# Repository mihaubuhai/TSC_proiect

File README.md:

# OpenBook e-book reader

## BOM - Bill of Materials

| Component                        | Datasheet | Vendor |
| ----------------------------------- | -------| --------|
| 112A-TAAR-R03_ATTEND                | [datasheet](https://www.attend.com.tw/en/product.php?act=view&id=253) | [vendor](https://www.digikey.com/en/products/detail/attend-technology/112A-TAAR-R03/17633923) |
| BD5229G-TR                          | [datasheet](https://www.digikey.ph/en/products/detail/rohm-semiconductor/BD5229G-TR/658502) | [vendor](https://www.digikey.ph/en/products/detail/rohm-semiconductor/BD5229G-TR/658502) |
| BUTTON_COSYOMV1                     | [datasheet](https://components101.com/switches/push-button) | [vendor](https://uk.farnell.com/wurth-elektronik/430182043816/switch-160gf-6x6mm-smd-4-3mm-act/dp/2065105?CMP=GRHB-OEMSECRETS101) |
| CPH3225A                            | [datasheet](https://www.digikey.com/en/products/detail/seiko-instruments/CPH3225A/8692444) | [vendor](https://www.digikey.com/en/products/detail/seiko-instruments/CPH3225A/8692444) |
| DS3231SN                            | [datasheet](https://www.digikey.com/en/products/detail/analog-devices-inc-maxim-integrated/DS3231SN/1197576) | [vendor](https://www.digikey.com/en/products/detail/analog-devices-inc-maxim-integrated/DS3231SN/1197576) |
| BME680                              | [datasheet](https://www.sparkfun.com/sparkfun-environmental-sensor-breakout-bme680-qwiic.html) | [vendor](https://www.sparkfun.com/sparkfun-environmental-sensor-breakout-bme680-qwiic.html) |
| MCP73831                            | [datasheet](https://www.microchip.com/en-us/product/mcp73831) | [vendor](https://www.microchipdirect.com/product/MCP73831T-2ADI/OT) |
| C6-WROOM-1-N8                       | [datasheet](https://www.espressif.com/sites/default/files/documentation/esp32-c6-wroom-1_wroom-1u_datasheet_en.pdf) | [vendor](https://www.adafruit.com/product/5671) |
| FH34SRJ-24S-0.5SH_99_               | [datasheet](https://www.hirose.com/product/p/CL0580-1255-6-99) | [vendor](https://www.hirose.com/product/p/CL0580-1255-6-99) |
| MAX17048G+T10                       | [datasheet](https://eu.mouser.com/ProductDetail/Analog-Devices-Maxim-Integrated/MAX17048G+T10?qs=D7PJwyCwLAoGnnn8jEPRBQ%3D%3D) | [vendor](https://eu.mouser.com/ProductDetail/Analog-Devices-Maxim-Integrated/MAX17048G+T10?qs=D7PJwyCwLAoGnnn8jEPRBQ%3D%3D) |
| MBR0530                             | [datasheet](https://www.digikey.com/en/products/detail/onsemi/MBR0530/1048783) | [vendor](https://www.digikey.com/en/products/detail/onsemi/MBR0530/1048783) |
| PGB1010603MR                        | [datasheet](https://www.digikey.com/en/products/detail/littelfuse-inc/PGB1010603MR/715755) | [vendor](https://www.digikey.com/en/products/detail/littelfuse-inc/PGB1010603MR/715755) |
| SAMACSYS_PARTS_USB4110-GF-A         | [datasheet](https://www.digikey.ro/en/products/detail/gct/USB4110-GF-A/10384547) | [vendor](https://www.digikey.ro/en/products/detail/gct/USB4110-GF-A/10384547) |
| SI1308EDL-T1-GE3                    | [datasheet](https://www.digikey.com/en/products/detail/vishay-siliconix/SI1308EDL-T1-GE3/4876435) | [vendor](https://www.digikey.com/en/products/detail/vishay-siliconix/SI1308EDL-T1-GE3/4876435) |
| SJ                                  | [datasheet](https://www.digikey.com/en/products/detail/cui-devices/SJ1-3514N/738685) | [vendor](https://www.digikey.com/en/products/detail/cui-devices/SJ1-3514N/738685) |
| USBLC6-2SC6Y                        | [datasheet](https://www.digikey.com/en/products/detail/stmicroelectronics/USBLC6-2SC6Y/2819177) | [vendor](https://www.digikey.com/en/products/detail/stmicroelectronics/USBLC6-2SC6Y/2819177) |
| W25Q512JVEIQ                        | [datasheet](https://www.digikey.com/en/products/detail/winbond-electronics/W25Q512JVEIQ/10244706) | [vendor](https://www.digikey.com/en/products/detail/winbond-electronics/W25Q512JVEIQ/10244706) |
| XC6220A331MR-G                      | [datasheet](https://www.digikey.com/en/products/detail/torex-semiconductor-ltd/XC6220B331MR-G/2138177) | [vendor](https://www.digikey.com/en/products/detail/torex-semiconductor-ltd/XC6220B331MR-G/2138177) |
| SD0805S020S1R0                      | [datasheet](https://www.digikey.com/en/products/detail/kyocera-avx/SD0805S020S1R0/3749517) | [vendor](https://www.digikey.com/en/products/detail/kyocera-avx/SD0805S020S1R0/3749517) |
| LTSPICE_C 100nF                     | [datasheet](https://www.digikey.com/en/products/detail/nextgen-components/0402B104K500HI/22601924) | [vendor](https://www.digikey.com/en/products/detail/nextgen-components/0402B104K500HI/22601924) |
| LTSPICE_C 10nF                      | [datasheet](https://www.amazon.com/ALLECIN-Electrolytic-Capacitor-0-2x0-43in-Capacitors/dp/B0CMQC587X/ref=sr_1_1_sspa?sr=8-1-spons&sp_csd=d2lkZ2V0TmFtZT1zcF9hdGY&psc=1) | [vendor](https://www.amazon.com/ALLECIN-Electrolytic-Capacitor-0-2x0-43in-Capacitors/dp/B0CMQC587X/ref=sr_1_1_sspa?sr=8-1-spons&sp_csd=d2lkZ2V0TmFtZT1zcF9hdGY&psc=1) |
| LTSPICE_C 4.7uF                     | [datasheet](https://www.amazon.com/ALLECIN-Electrolytic-Capacitor-0-2x0-43in-Capacitors/dp/B0CMQC587X/ref=sr_1_1_sspa?sr=8-1-spons&sp_csd=d2lkZ2V0TmFtZT1zcF9hdGY&psc=1) | [vendor](https://www.amazon.com/ALLECIN-Electrolytic-Capacitor-0-2x0-43in-Capacitors/dp/B0CMQC587X/ref=sr_1_1_sspa?sr=8-1-spons&sp_csd=d2lkZ2V0TmFtZT1zcF9hdGY&psc=1) |
| LTSPICE_C 1uF                       | [datasheet](https://www.amazon.com/ALLECIN-Electrolytic-Capacitor-0-2x0-43in-Capacitors/dp/B0CMQC587X/ref=sr_1_1_sspa?sr=8-1-spons&sp_csd=d2lkZ2V0TmFtZT1zcF9hdGY&psc=1) | [vendor](https://www.amazon.com/ALLECIN-Electrolytic-Capacitor-0-2x0-43in-Capacitors/dp/B0CMQC587X/ref=sr_1_1_sspa?sr=8-1-spons&sp_csd=d2lkZ2V0TmFtZT1zcF9hdGY&psc=1) |
| LTSPICE_C 0.1uF                     | [datasheet](https://www.digikey.com/en/products/detail/samsung-electro-mechanics/CL10E104KC8VPNC/20498486) | [vendor](https://www.digikey.com/en/products/detail/samsung-electro-mechanics/CL10E104KC8VPNC/20498486) |
| ADAFRUIT_LED                        | [datasheet](https://www.adafruit.com/product/4684) | [vendor](https://www.adafruit.com/product/4684) |
| ESP32_VARISTOR                      | [datasheet](https://uk.rs-online.com/web/p/varistors/9012743) | [vendor](https://uk.rs-online.com/web/p/varistors/9012743) |
| CT3528 (RCL_CPOL-EU) 100uF          | [datasheet](https://www.datasheetarchive.com/?q=ct3528) | [vendor](https://ro.mouser.com/ProductDetail/Panasonic/EEU-FS1K101L?qs=sGAEpiMZZMvwFf0viD3Y3fHxNcSaiftwbgqrEa58hlq7Mz20qWHEdw%3D%3D) |
| DMG2305UX-7 20V/4.2A/52mO/1.4W      | [datasheet](https://www.digikey.com/en/products/detail/diodes-incorporated/DMG2305UX-7/4340667) | [vendor](https://www.digikey.com/en/products/detail/diodes-incorporated/DMG2305UX-7/4340667) |
| IND-4828-WE-TPC-WRE                 | [datasheet](https://www.axel-gl.com/en/asone/d/64-0172-48/) | [vendor](https://www.axel-gl.com/en/asone/d/64-0172-48/) |
| JS-1MM(QWIIC_CONNECTOR)             | [datasheet](https://www.sparkfun.com/qwiic-jst-connector-smd-4-pin-horizontal.html) | [vendor](https://www.sparkfun.com/qwiic-jst-connector-smd-4-pin-horizontal.html) |
| LTSPICE_R 5k1                      | [datasheet](https://www.vishay.com/docs/53046/pfrr.pdf) | [vendor](https://www.amazon.com/BOJACK-Values-Resistor-Resistors-Assortment/dp/B08FD1XVL6/ref=sr_1_1_sspa?sr=8-1-spons&sp_csd=d2lkZ2V0TmFtZT1zcF9hdGY) |
| LTSPICE_R 100k                     | [datasheet](https://www.vishay.com/docs/53046/pfrr.pdf) | [vendor](https://www.amazon.com/BOJACK-Values-Resistor-Resistors-Assortment/dp/B08FD1XVL6/ref=sr_1_1_sspa?sr=8-1-spons&sp_csd=d2lkZ2V0TmFtZT1zcF9hdGY) |
| LTSPICE_R 2.2                      | [datasheet](https://www.vishay.com/docs/53046/pfrr.pdf) | [vendor](https://www.amazon.com/BOJACK-Values-Resistor-Resistors-Assortment/dp/B08FD1XVL6/ref=sr_1_1_sspa?sr=8-1-spons&sp_csd=d2lkZ2V0TmFtZT1zcF9hdGY) |
| LTSPICE_R 10k                      | [datasheet](https://www.vishay.com/docs/53046/pfrr.pdf) | [vendor](https://www.amazon.com/BOJACK-Values-Resistor-Resistors-Assortment/dp/B08FD1XVL6/ref=sr_1_1_sspa?sr=8-1-spons&sp_csd=d2lkZ2V0TmFtZT1zcF9hdGY) |
| LTSPICE_R 0.47                     | [datashet](https://www.vishay.com/docs/53046/pfrr.pdf) | [vendor](https://www.amazon.com/BOJACK-Values-Resistor-Resistors-Assortment/dp/B08FD1XVL6/ref=sr_1_1_sspa?sr=8-1-spons&sp_csd=d2lkZ2V0TmFtZT1zcF9hdGY) |
| LTSPICE_R 2k                       | [datasheet](https://www.vishay.com/docs/53046/pfrr.pdf) | [vendor](https://www.amazon.com/BOJACK-Values-Resistor-Resistors-Assortment/dp/B08FD1XVL6/ref=sr_1_1_sspa?sr=8-1-spons&sp_csd=d2lkZ2V0TmFtZT1zcF9hdGY) |
| LTSPICE_R 200                      | [datasheet](https://www.vishay.com/docs/53046/pfrr.pdf) | [vendor](https://www.amazon.com/BOJACK-Values-Resistor-Resistors-Assortment/dp/B08FD1XVL6/ref=sr_1_1_sspa?sr=8-1-spons&sp_csd=d2lkZ2V0TmFtZT1zcF9hdGY) |
| LTSPICE_R 15                       | [datasheet](https://www.vishay.com/docs/53046/pfrr.pdf) | [vendor](https://www.amazon.com/BOJACK-Values-Resistor-Resistors-Assortment/dp/B08FD1XVL6/ref=sr_1_1_sspa?sr=8-1-spons&sp_csd=d2lkZ2V0TmFtZT1zcF9hdGY) |
| Test Pad TP20R                      | [datasheet](https://us.misumi-ec.com/vona2/detail/221005496391/?HissuCode=TP20R-24) | [vendor](https://us.misumi-ec.com/vona2/detail/221005496391/?HissuCode=TP20R-24) |

#
```
        Microcontroler: ESP32-C6-WROOM-1-N1 (U2). Acesta este un microcontroler puternic cu conectivitate
    Wi-Fi, Bluetooth, care gestionează procesarea datelor, comunicațiile și controlul general
    al dispozitivului.

    Alimentare:
        Un conector USB-C furnizează intrarea principală de alimentare.
        Un regulator LDO de tensiune (IC4, XC6220A331MR-G) asigură o tensiune stabilă pentru componente.
        Un controler de încărcare pentru baterii Li-Po (MCP73831) gestionează încărcarea bateriei,
            permițând funcționarea autonomă.
        MAX17048G+T10 (U4) monitorizează nivelul de încărcare al bateriei.

        Stocare de date: O memorie Flash NOR externă (U1, W25Q512JVEIQ) oferă stocare non-volatilă
    pentru jurnalizarea datelor, firmware sau alte informații. Este prezent și un slot pentru card SD
    pentru stocare detașabilă.

        Ceas în timp real (RTC): Modulul RTC DS3231SN (U3) menține o măsurare precisă a timpului,
    esențială pentru marcarea temporală a datelor. Un supercondensator (C10) oferă alimentare de
    rezervă pentru RTC.

        Senzori de mediu: Un senzor BME688 măsoară parametrii de mediu (temperatură, umiditate).

        Afișaj: Un ecran E-Paper este utilizat pentru afișarea informațiilor. Interfața cu ecranul
    include un conector (FH34SR-24S-0.5SH_99) și circuitele de susținere.

    Interfață cu utilizatorul:
        Butoanele Boot și Reset permit controlul sistemului și actualizări de firmware.
        Un buton "Change" oferă o intrare din partea utilizatorului.

    Comunicație: ESP32-C6 oferă capabilități de comunicare wireless (Wi-Fi, Bluetooth).

    Alte componente:
        Dispozitive de protecție ESD (USBLC6-2SC6Y, PEMF050.1) protejează circuitul de descărcări
            electrostatice.
        Paduri de test sunt incluse pentru depanare și testare.
        Un conector Qwiic/Stemma QT permite conectarea ușoară a dispozitivelor externe I2C.
```

### Utilizarea pinilor ESP32-C6
```
    Pini de alimentare: Pinii conectați la 3V3 și GND furnizează alimentare și împământare pentru ESP32-C6.

        Comunicație USB: Pinii conectați la conectorul USB-C (prin protecție ESD) sunt utilizați pentru
    comunicația și alimentarea prin USB.

        Interfață card SD: Pinii conectați la slotul pentru card SD (DAT0, DAT1, DAT2, CMD, CLK) sunt
    utilizați pentru interfața cu cardul SD.

        Comunicație SPI: Pinii conectați la memoria Flash externă (W25Q512JVEIQ) (CS, SCK, DO, DI) sunt
    utilizați pentru comunicația SPI.

        Comunicație I2C: Pinii conectați la RTC (DS3231SN) și la conectorul Qwiic (SDA, SCL) sunt utilizați
    pentru comunicația I2C. Senzorul BME688 utilizează și el I2C, prin tag-ul I2C_PW.

    Pini GPIO:
        Pinii conectați la butoanele Boot, Reset și Change sunt utilizați ca pini de intrare/ieșire
            generală (GPIO) pentru a citi starea butoanelor.
        Pinii conectați la interfața ecranului E-Paper sunt GPIO-uri utilizate pentru a controla afișajul.
        Alți pini GPIO pot fi utilizați pentru semnale de control sau indicatori de stare.
```

# ERORI ACCEPTATE
```
        Am acceptat erorile cauzate de nerutarea pinilor GND deoarece am deja 2 planuri de masă puse pe pe placă,
    iar eu consider că nu este necesară rutarea acestor pini între ei, în final ei legându-se la masă.
```

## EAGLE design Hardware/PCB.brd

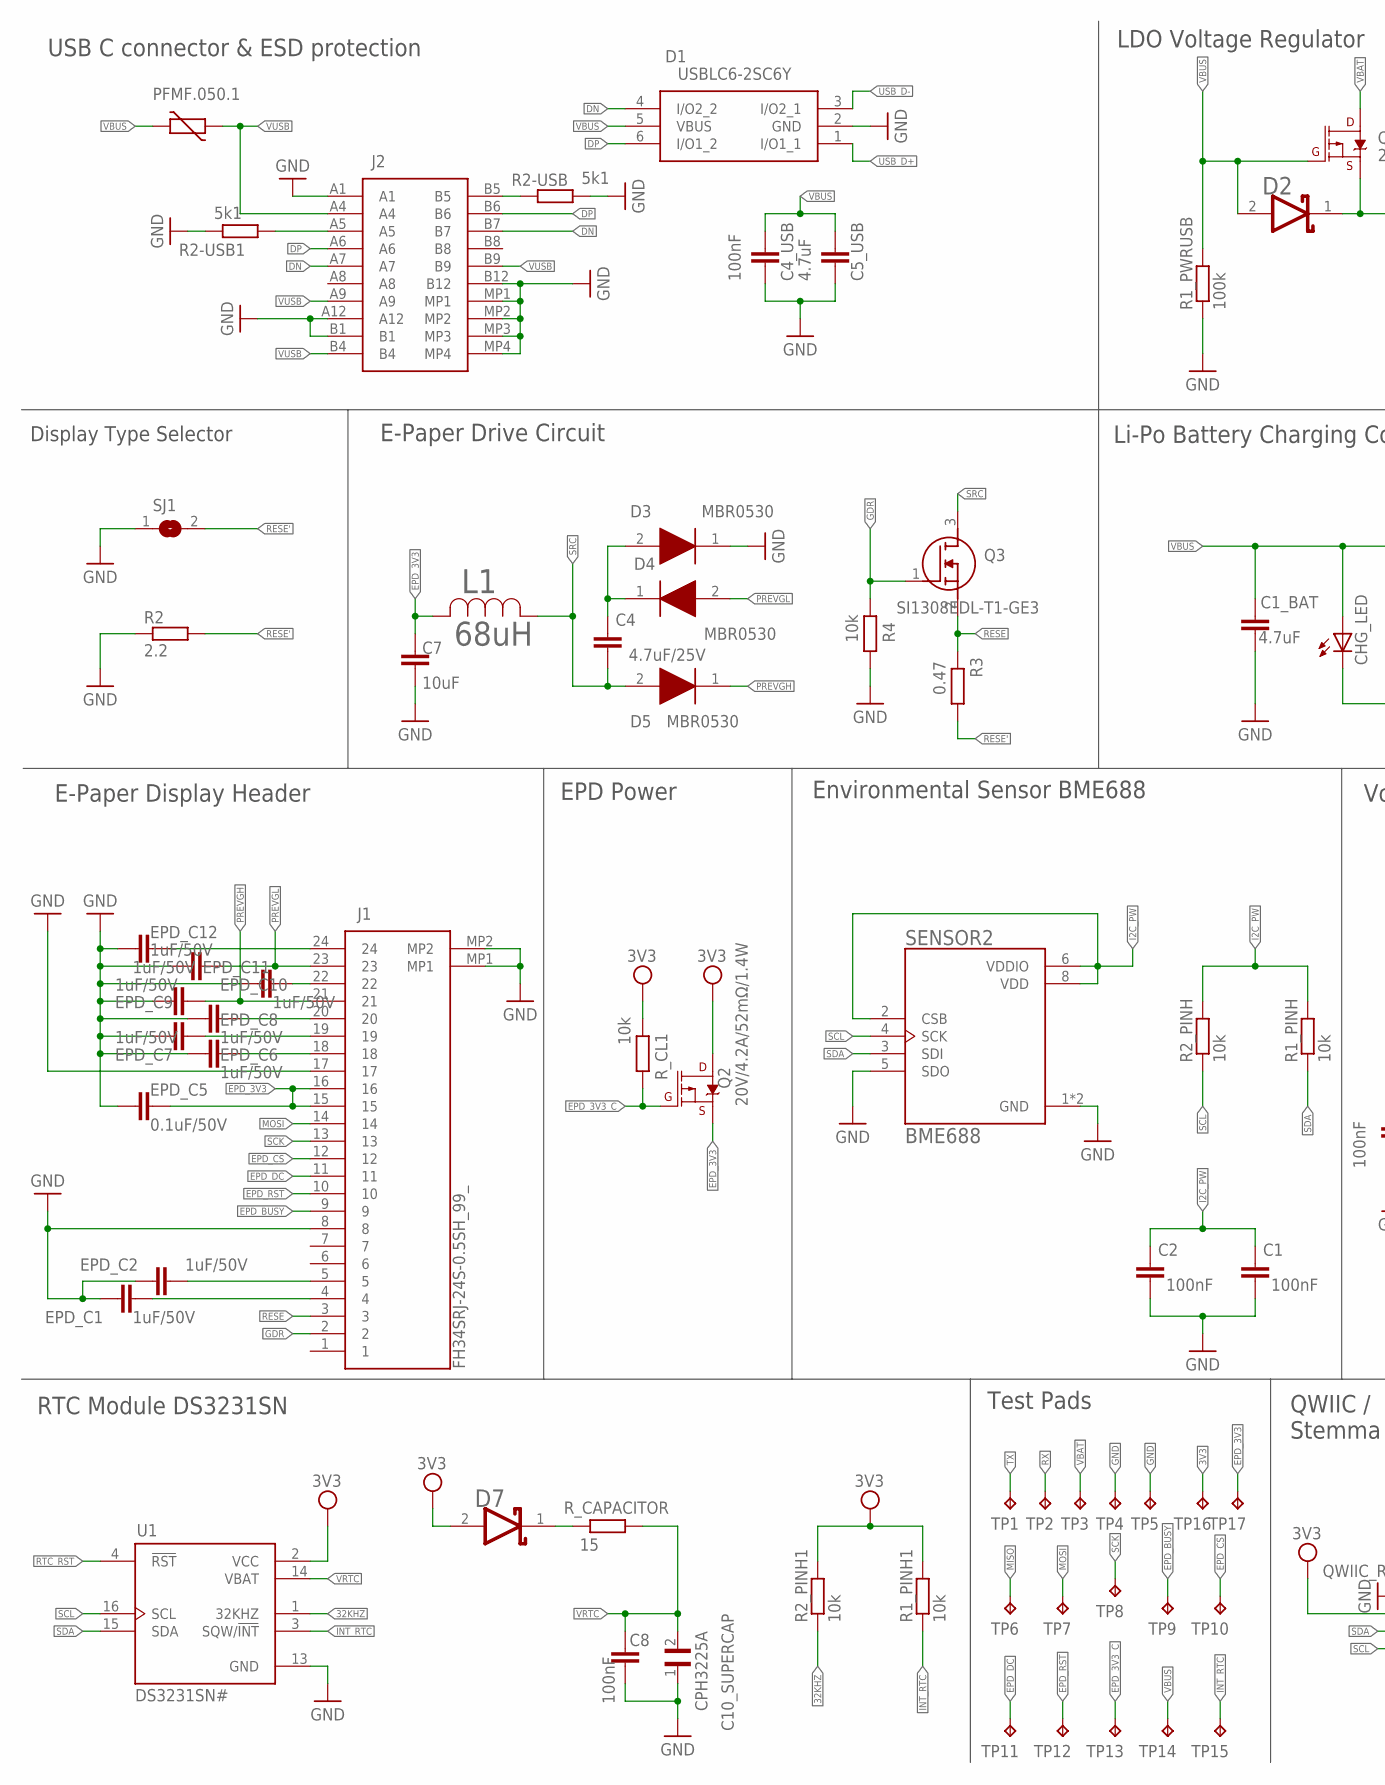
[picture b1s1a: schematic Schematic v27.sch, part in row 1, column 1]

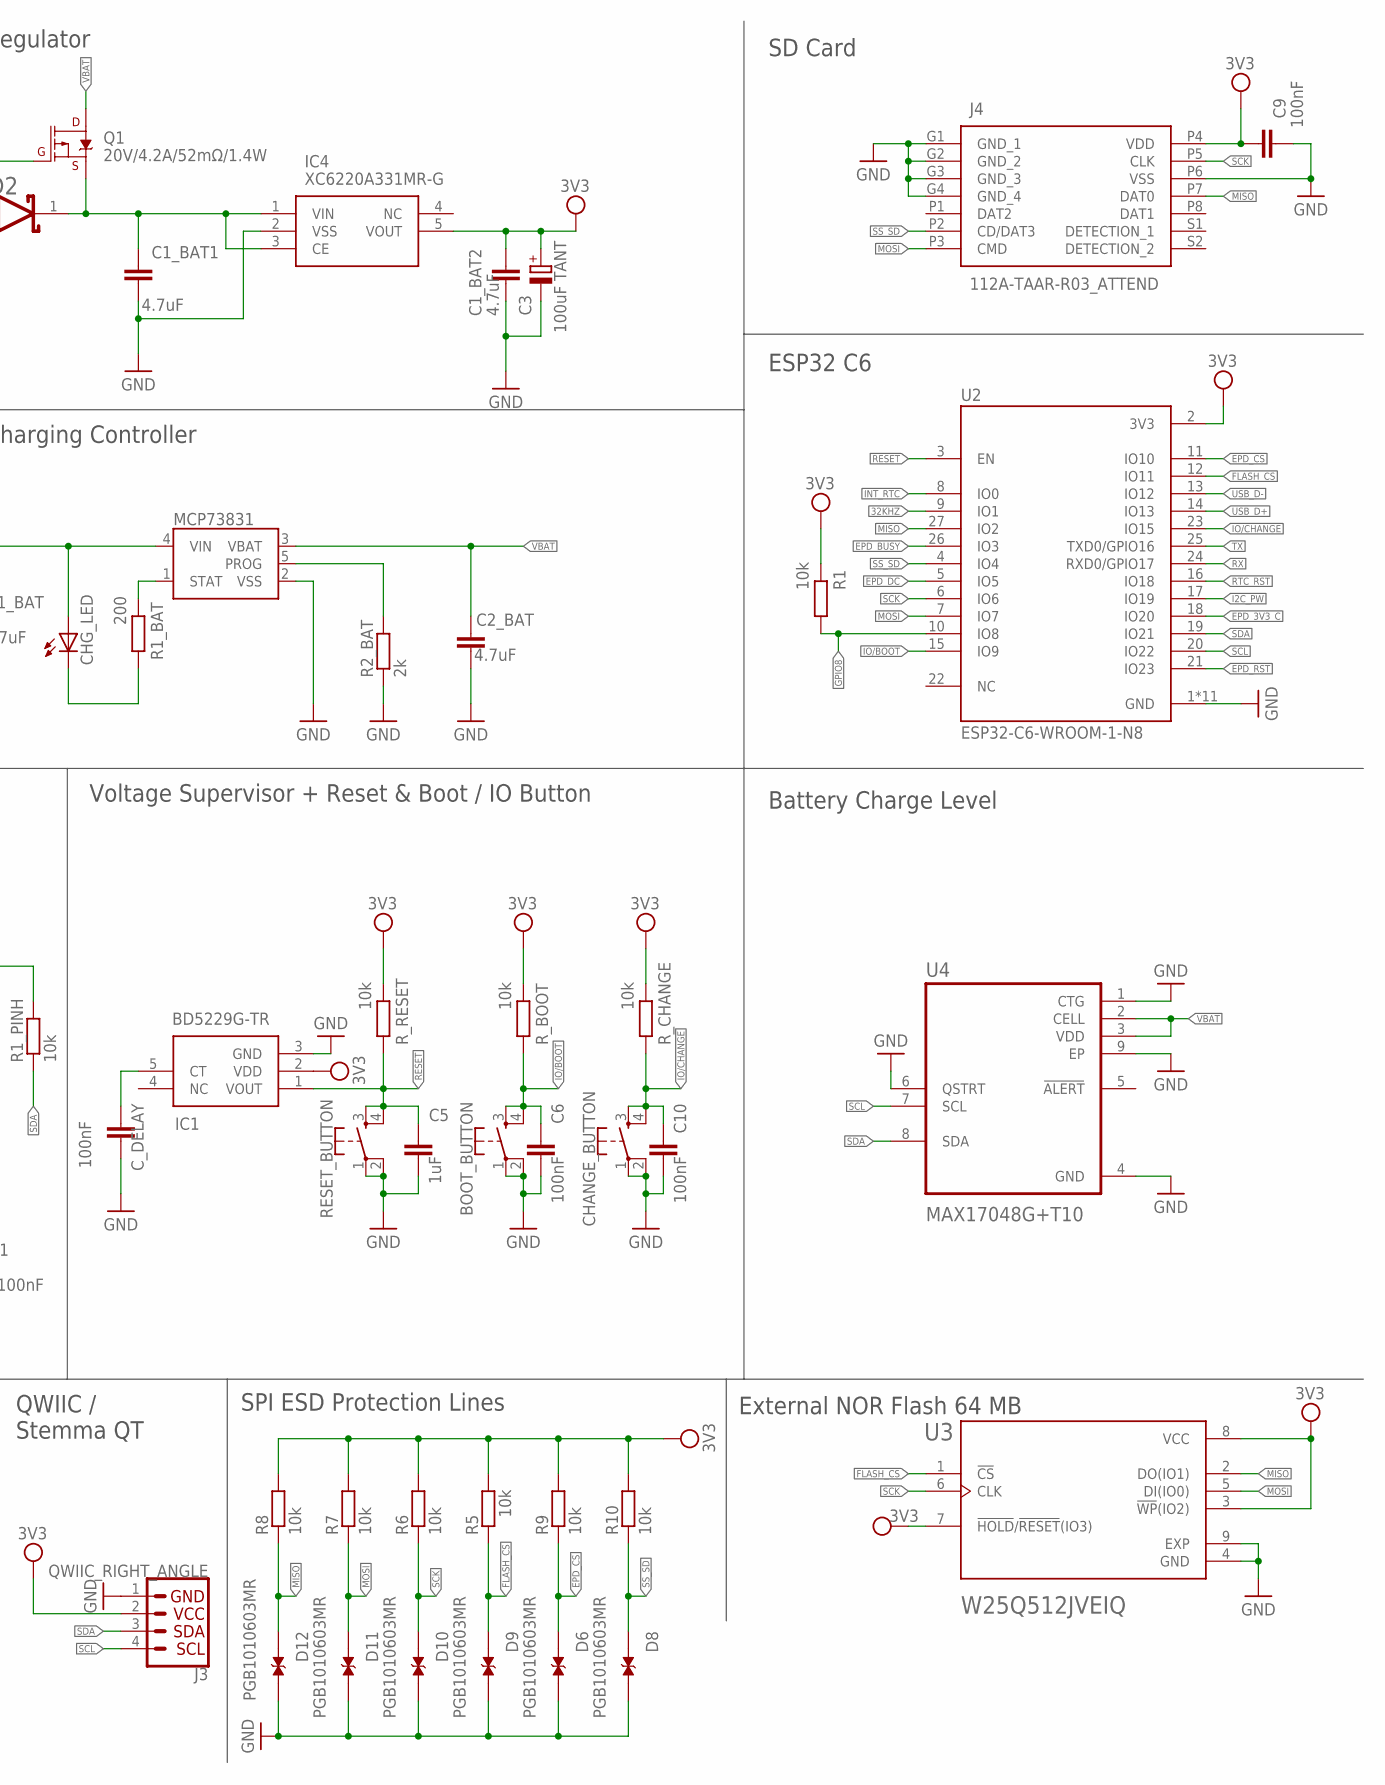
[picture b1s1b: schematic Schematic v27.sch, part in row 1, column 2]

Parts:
BOOT_BUTTON: BUTTON_CUSYOMV1; MYBUTTON
C1, C2, C4_USB, C6, C8, C9, C10: 100nF; ESP32_WROVER_EAGLE-LTSPICE_C0402
C1_BAT, C1_BAT1, C1_BAT2, C2_BAT, C5_USB: 4.7uF; ESP32_WROVER_EAGLE-LTSPICE_C0402
C3: 100uF TANT; RCL_CT3528
C4: 4.7uF/25V; ESP32_WROVER_EAGLE-LTSPICE_C0402
C5: 1uF; ESP32_WROVER_EAGLE-LTSPICE_C0402
C7: 10uF; ESP32_WROVER_EAGLE-LTSPICE_C0402
C10_SUPERCAP: CPH3225A; CAPCP3225X100N
CHANGE_BUTTON: BUTTON_CUSYOMV1; MYBUTTON
CHG_LED: ADAFRUIT_LEDCHIP-LED0603; ADAFRUIT_CHIP-LED0603
C_DELAY: 100nF; ESP32_WROVER_EAGLE-LTSPICE_C0402
D1: USBLC6-2SC6Y; SOT95P280X145-6N
D2, D7: ESP32_WROVER_AVX---SD0805S020S1R0_AVX_SD0805S020S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; ESP32_WROVER_AVX---SD0805S020S1R0_AVX_SD0805S020S1R0_0
D3, D4, D5: MBR0530; SOD3716X135N
D6, D8, D9, D10, D11, D12: PGB1010603MR; DIOC1608X36N
EPD_C1, EPD_C2, EPD_C6, EPD_C7, EPD_C8, EPD_C9, EPD_C10, EPD_C11, EPD_C12: 1uF/50V; ESP32_WROVER_EAGLE-LTSPICE_C0402
EPD_C5: 0.1uF/50V; ESP32_WROVER_EAGLE-LTSPICE_C0402
IC1: BD5229G-TR; SOT95P280X125-5N
IC4: XC6220A331MR-G; SOT95P280X120-5N
J1: FH34SRJ-24S-0.5SH_99_; FH34SRJ24S05SH99
J2: SAMACSYS_PARTS_USB4110-GF-A; SAMACSYS_PARTS_USB4110GFA
J3: QWIIC_RIGHT_ANGLE; JST04_1MM_RA
J4: 112A-TAAR-R03_ATTEND; 112ATAARR03ATTEND
L1: 68uH; IND_4828-WE-TPC_WRE
MCP73831: ESP32_WROVER_SPARKFUN-IC-POWER_MCP73831; ESP32_WROVER_SPARKFUN-IC-POWER_SOT23-5
PFMF.050.1: ESP32C6_VARISTORCN1812; ESP32C6_VARISTOR_CT/CN1812
Q1, Q2: 20V/4.2A/52mΩ/1.4W; ESP32_WROVER_SPARKFUN-DISCRETESEMI_SOT23-3
Q3: SI1308EDL-T1-GE3; SOT65P210X110-3N
R1, R1_PINH, R1_PINH1, R2_PINH, R2_PINH1, R4, R5, R6, R7, R8, R9, R10: 10k; ESP32_WROVER_EAGLE-LTSPICE_R0402
R1_BAT: 200; ESP32_WROVER_EAGLE-LTSPICE_R0402
R1_PWRUSB: 100k; ESP32_WROVER_EAGLE-LTSPICE_R0402
R2: 2.2; ESP32_WROVER_EAGLE-LTSPICE_R0402
R2-USB, R2-USB1: 5k1; ESP32_WROVER_EAGLE-LTSPICE_R0402
R2_BAT: 2k; ESP32_WROVER_EAGLE-LTSPICE_R0402
R3: 0.47; ESP32_WROVER_EAGLE-LTSPICE_R0402
RESET_BUTTON: BUTTON_CUSYOMV1; MYBUTTON
R_BOOT: 10k; ESP32_WROVER_EAGLE-LTSPICE_R0402
R_CAPACITOR: 15; ESP32_WROVER_EAGLE-LTSPICE_R0402
R_CHANGE: 10k; ESP32_WROVER_EAGLE-LTSPICE_R0402
R_CL1: 10k; ESP32_WROVER_EAGLE-LTSPICE_R0402
R_RESET: 10k; ESP32_WROVER_EAGLE-LTSPICE_R0402
SENSOR2: BME688; ESP32_WROVER_BME680_PSON80P300X300X100-8N
SJ1: SJ
TP1, TP2, TP3, TP4, TP5, TP6, TP7, TP8, TP9, TP10, TP11, TP12, TP13, TP14, TP15, TP16, TP17: TPTP20R; TP20R
U1: DS3231SN#; SOIC127P1032X265-16N
U2: ESP32-C6-WROOM-1-N8; XCVR_ESP32-C6-WROOM-1-N8
U3: W25Q512JVEIQ; SON127P600X800X80-9N
U4: MAX17048G+T10; SON50P200X200X80-9N

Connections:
3V3: C1_BAT2.1, C3.+, C9.1, D7.2 (ANODE), IC1.2 (VDD), IC4.5 (VOUT), J3.2, J4.P4 (VDD), Q2.3 (D), R1.2, R1_PINH1.2, R2_PINH1.2, R5.2, R6.2, R7.2, R8.2, R9.2, R10.2, R_BOOT.2, R_CHANGE.2, R_CL1.2, R_RESET.2, TP16.TP, U1.2 (VCC), U2.2 (3V3), U3.3 (!WP!(IO2)), U3.7 (!HOLD!/!RESET!(IO3)), U3.8 (VCC)
32KHZ: R2_PINH1.1, U1.1 (32KHZ), U2.9 (IO1)
DN: D1.4 (I/O2_2), J2.A7, J2.B7
DP: D1.6 (I/O1_2), J2.A6, J2.B6
EPD_3V3: C7.2, EPD_C5.2, J1.15, J1.16, L1.2, Q2.2 (S), TP17.TP
EPD_3V3_C: Q2.1 (G), R_CL1.1, TP13.TP, U2.18 (IO20)
EPD_BUSY: J1.9, TP9.TP, U2.26 (IO3)
EPD_CS: D6.1, J1.12, R9.1, TP10.TP, U2.11 (IO10)
EPD_DC: J1.11, TP11.TP, U2.5 (IO5)
EPD_RST: J1.10, TP12.TP, U2.21 (IO23)
FLASH_CS: D9.1, R5.1, U2.12 (IO11), U3.1 (!CS)
GDR: J1.2, Q3.1 (G), R4.2
GND: BOOT_BUTTON.1, BOOT_BUTTON.2, C1.2, C1_BAT.2, C1_BAT1.2, C1_BAT2.2, C2.2, C2_BAT.2, C3.-, C4_USB.2, C5.2, C5_USB.2, C6.2, C7.1, C8.1, C9.2, C10.2, C10_SUPERCAP.1, CHANGE_BUTTON.1, CHANGE_BUTTON.2, C_DELAY.2, D1.2 (GND), D3.1 (K), D6.2, D8.2, D9.2, D10.2, D11.2, D12.2, EPD_C1.1, EPD_C2.1, EPD_C5.1, EPD_C6.1, EPD_C7.1, EPD_C8.1, EPD_C9.1, EPD_C10.1, EPD_C11.1, EPD_C12.1, IC1.3 (GND), IC4.2 (VSS), J1.8, J1.17, J1.MP1, J1.MP2, J2.A1, J2.A12, J2.B1, J2.B12, J2.MP1, J2.MP2, J2.MP3, J2.MP4, J3.1, J4.G1 (GND_1), J4.G2 (GND_2), J4.G3 (GND_3), J4.G4 (GND_4), J4.P6 (VSS), MCP73831.2 (VSS), R1_PWRUSB.1, R2.1, R2-USB.2, R2-USB1.1, R2_BAT.1, R4.1, RESET_BUTTON.1, RESET_BUTTON.2, SENSOR2.1 (GND), SENSOR2.5 (SDO), SENSOR2.7 (GND), SJ1.1, TP4.TP, TP5.TP, U1.13 (GND), U2.1 (GND), U2.28 (GND), U2.29_1 (GND), U2.29_2 (GND), U2.29_3 (GND)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
GPIO8: R1.1, U2.10 (IO8)
I2C_PW: C1.1, C2.1, R1_PINH.2, R2_PINH.2, SENSOR2.2 (CSB), SENSOR2.6 (VDDIO), SENSOR2.8 (VDD), U2.17 (IO19)
INT_RTC: R1_PINH1.1, TP15.TP, U1.3 (SQW/!INT), U2.8 (IO0)
IO/BOOT: BOOT_BUTTON.3, BOOT_BUTTON.4, C6.1, R_BOOT.1, U2.15 (IO9)
IO/CHANGE: C10.1, CHANGE_BUTTON.3, CHANGE_BUTTON.4, R_CHANGE.1, U2.23 (IO15)
MISO: D12.1, J4.P7 (DAT0), R8.1, TP6.TP, U2.27 (IO2), U3.2 (DO(IO1))
MOSI: D11.1, J1.14, J4.P3 (CMD), R7.1, TP7.TP, U2.7 (IO7), U3.5 (DI(IO0))
unnamed: J2.B5, R2-USB.1
unnamed: J2.A5, R2-USB1.2
unnamed: C1_BAT1.1, D2.1 (CATHODE), IC4.1 (VIN), IC4.3 (CE), Q1.2 (S)
unnamed: MCP73831.1 (STAT), R1_BAT.2
unnamed: MCP73831.5 (PROG), R2_BAT.2
unnamed: CHG_LED.C, R1_BAT.1
unnamed: C4.1, D3.2 (A), D4.1 (K)
unnamed: EPD_C6.2, J1.18
unnamed: EPD_C7.2, J1.19
unnamed: EPD_C8.2, J1.20
unnamed: C_DELAY.1, IC1.5 (CT)
unnamed: EPD_C10.2, J1.22
unnamed: D7.1 (CATHODE), R_CAPACITOR.2
unnamed: EPD_C12.2, J1.24
unnamed: EPD_C1.2, J1.4
unnamed: EPD_C2.2, J1.5
PREVGH: D5.1 (K), EPD_C9.2, J1.21
PREVGL: D4.2 (A), EPD_C11.2, J1.23
RESE: J1.3, Q3.2 (S), R3.2
RESE': R2.2, R3.1, SJ1.2
RESET: C5.1, IC1.1 (VOUT), RESET_BUTTON.3, RESET_BUTTON.4, R_RESET.1, U2.3 (EN)
RTC_RST: U1.4 (!RST), U2.16 (IO18)
RX: TP2.TP, U2.24 (RXD0/GPIO17)
SCK: D10.1, J1.13, J4.P5 (CLK), R6.1, TP8.TP, U2.6 (IO6), U3.6 (CLK)
SCL: J3.4, R2_PINH.1, SENSOR2.4 (SCK), U1.16 (SCL), U2.20 (IO22), U4.7 (SCL)
SDA: J3.3, R1_PINH.1, SENSOR2.3 (SDI), U1.15 (SDA), U2.19 (IO21), U4.8 (SDA)
SRC: C4.2, D5.2 (A), L1.1, Q3.3 (D)
SS_SD: D8.1, J4.P2 (CD/DAT3), R10.1, U2.4 (IO4)
TX: TP1.TP, U2.25 (TXD0/GPIO16)
USB_D+: D1.1 (I/O1_1), U2.14 (IO13)
USB_D-: D1.3 (I/O2_1), U2.13 (IO12)
VBAT: C2_BAT.1, MCP73831.3 (VBAT), Q1.3 (D), TP3.TP, U4.2 (CELL), U4.3 (VDD)
VBUS: C1_BAT.1, C4_USB.1, C5_USB.1, CHG_LED.A, D1.5 (VBUS), D2.2 (ANODE), MCP73831.4 (VIN), PFMF.050.1.2, Q1.1 (G), R1_PWRUSB.2, TP14.TP
VRTC: C8.2, C10_SUPERCAP.2, R_CAPACITOR.1, U1.14 (VBAT)
VUSB: J2.A4, J2.A9, J2.B4, J2.B9, PFMF.050.1.1

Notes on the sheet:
USB C connector & ESD protection
LDO Voltage Regulator
SD Card
ESP32 C6
Li-Po Battery Charging Controller
E-Paper Drive Circuit
Display Type Selector
E-Paper Display Header
EPD Power
Environmental Sensor BME688
Voltage Supervisor + Reset & Boot / IO Button
Battery Charge Level
RTC Module DS3231SN
Test Pads
QWIIC / Stemma QT
SPI ESD Protection Lines
External NOR Flash 64 MB

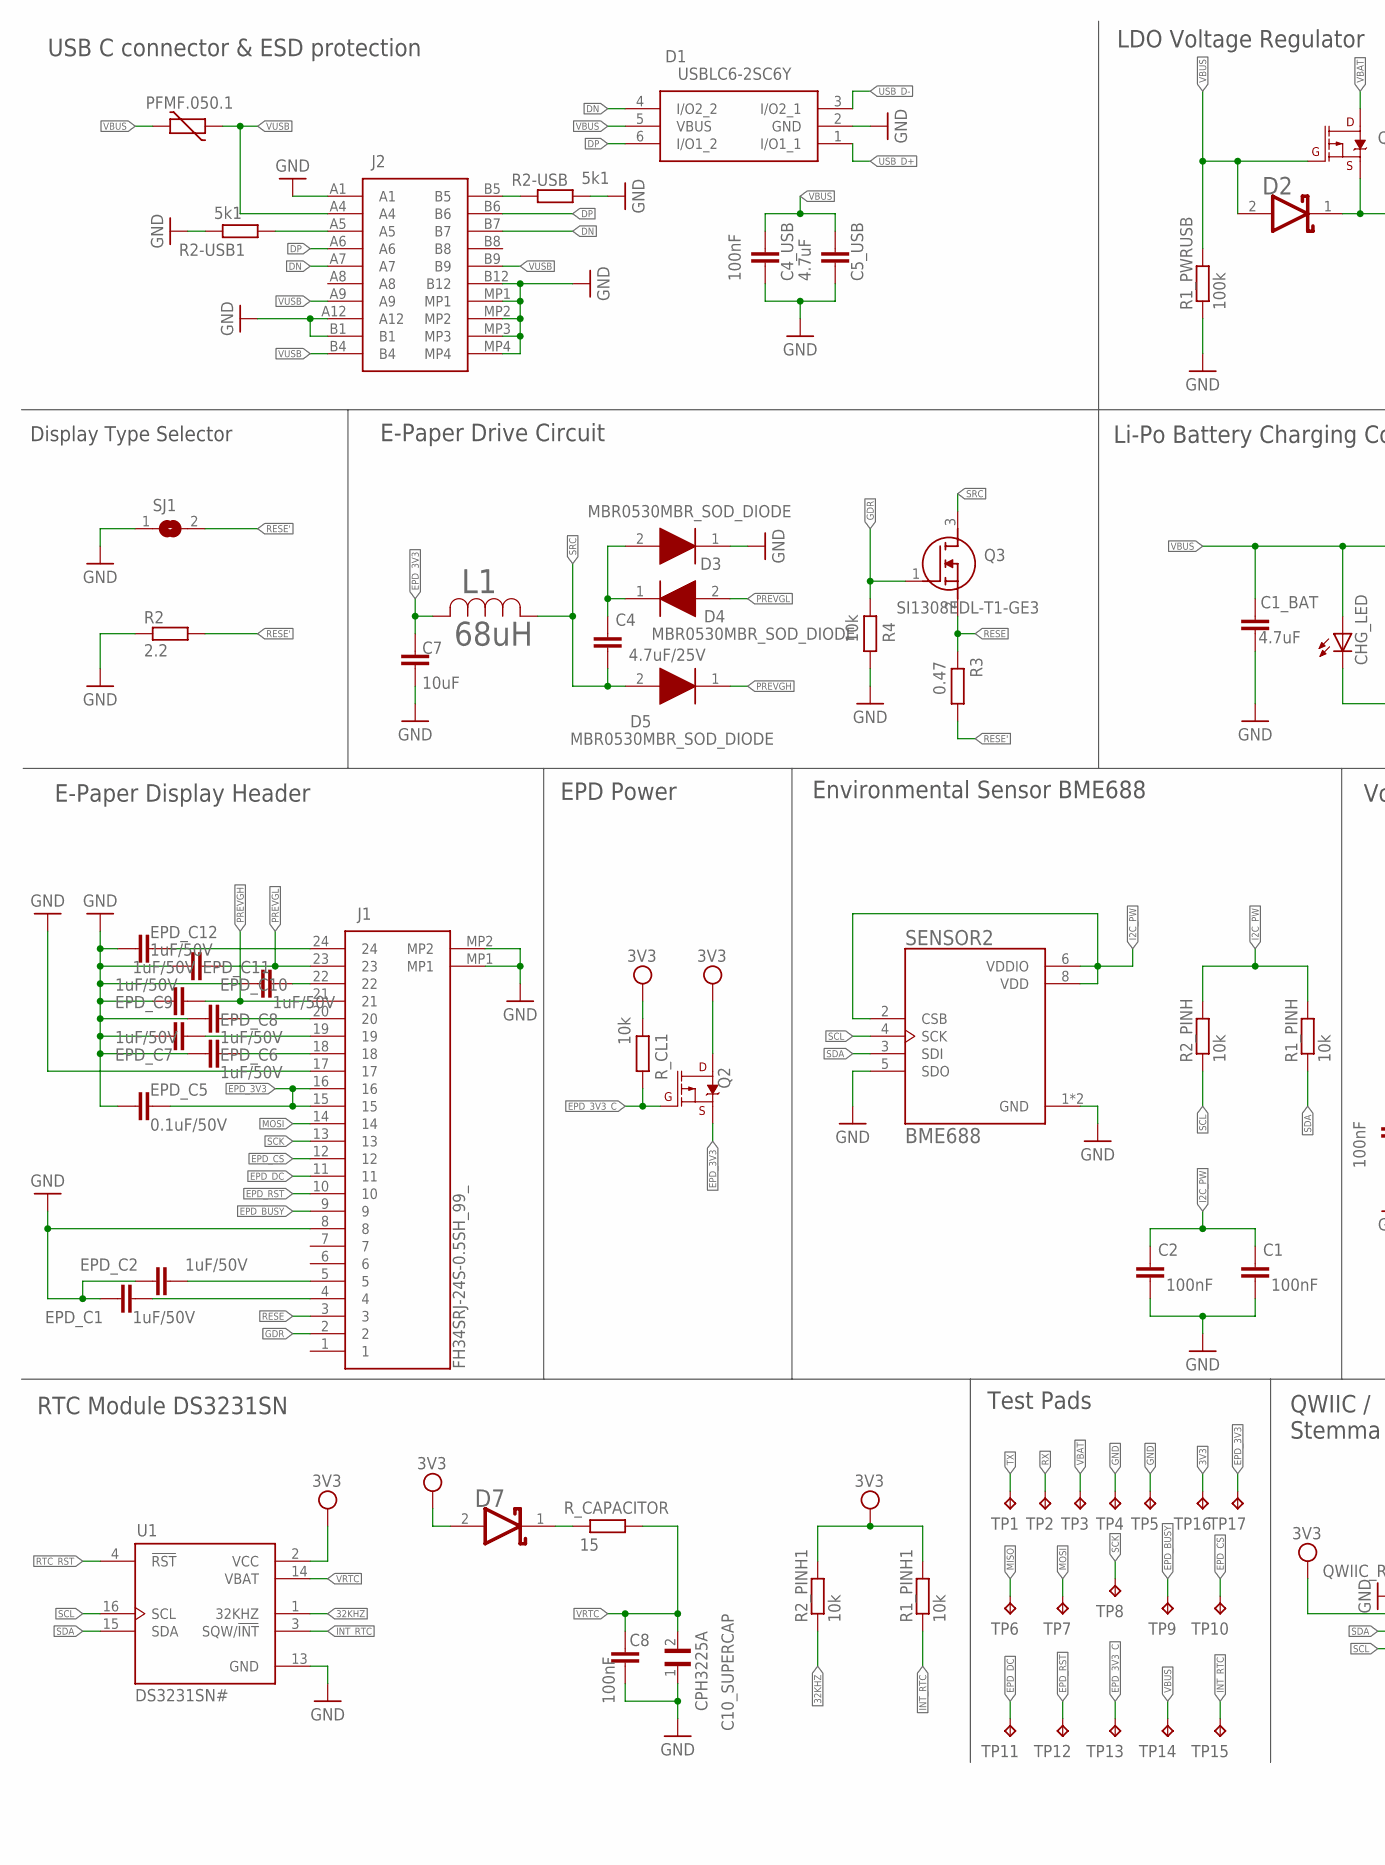
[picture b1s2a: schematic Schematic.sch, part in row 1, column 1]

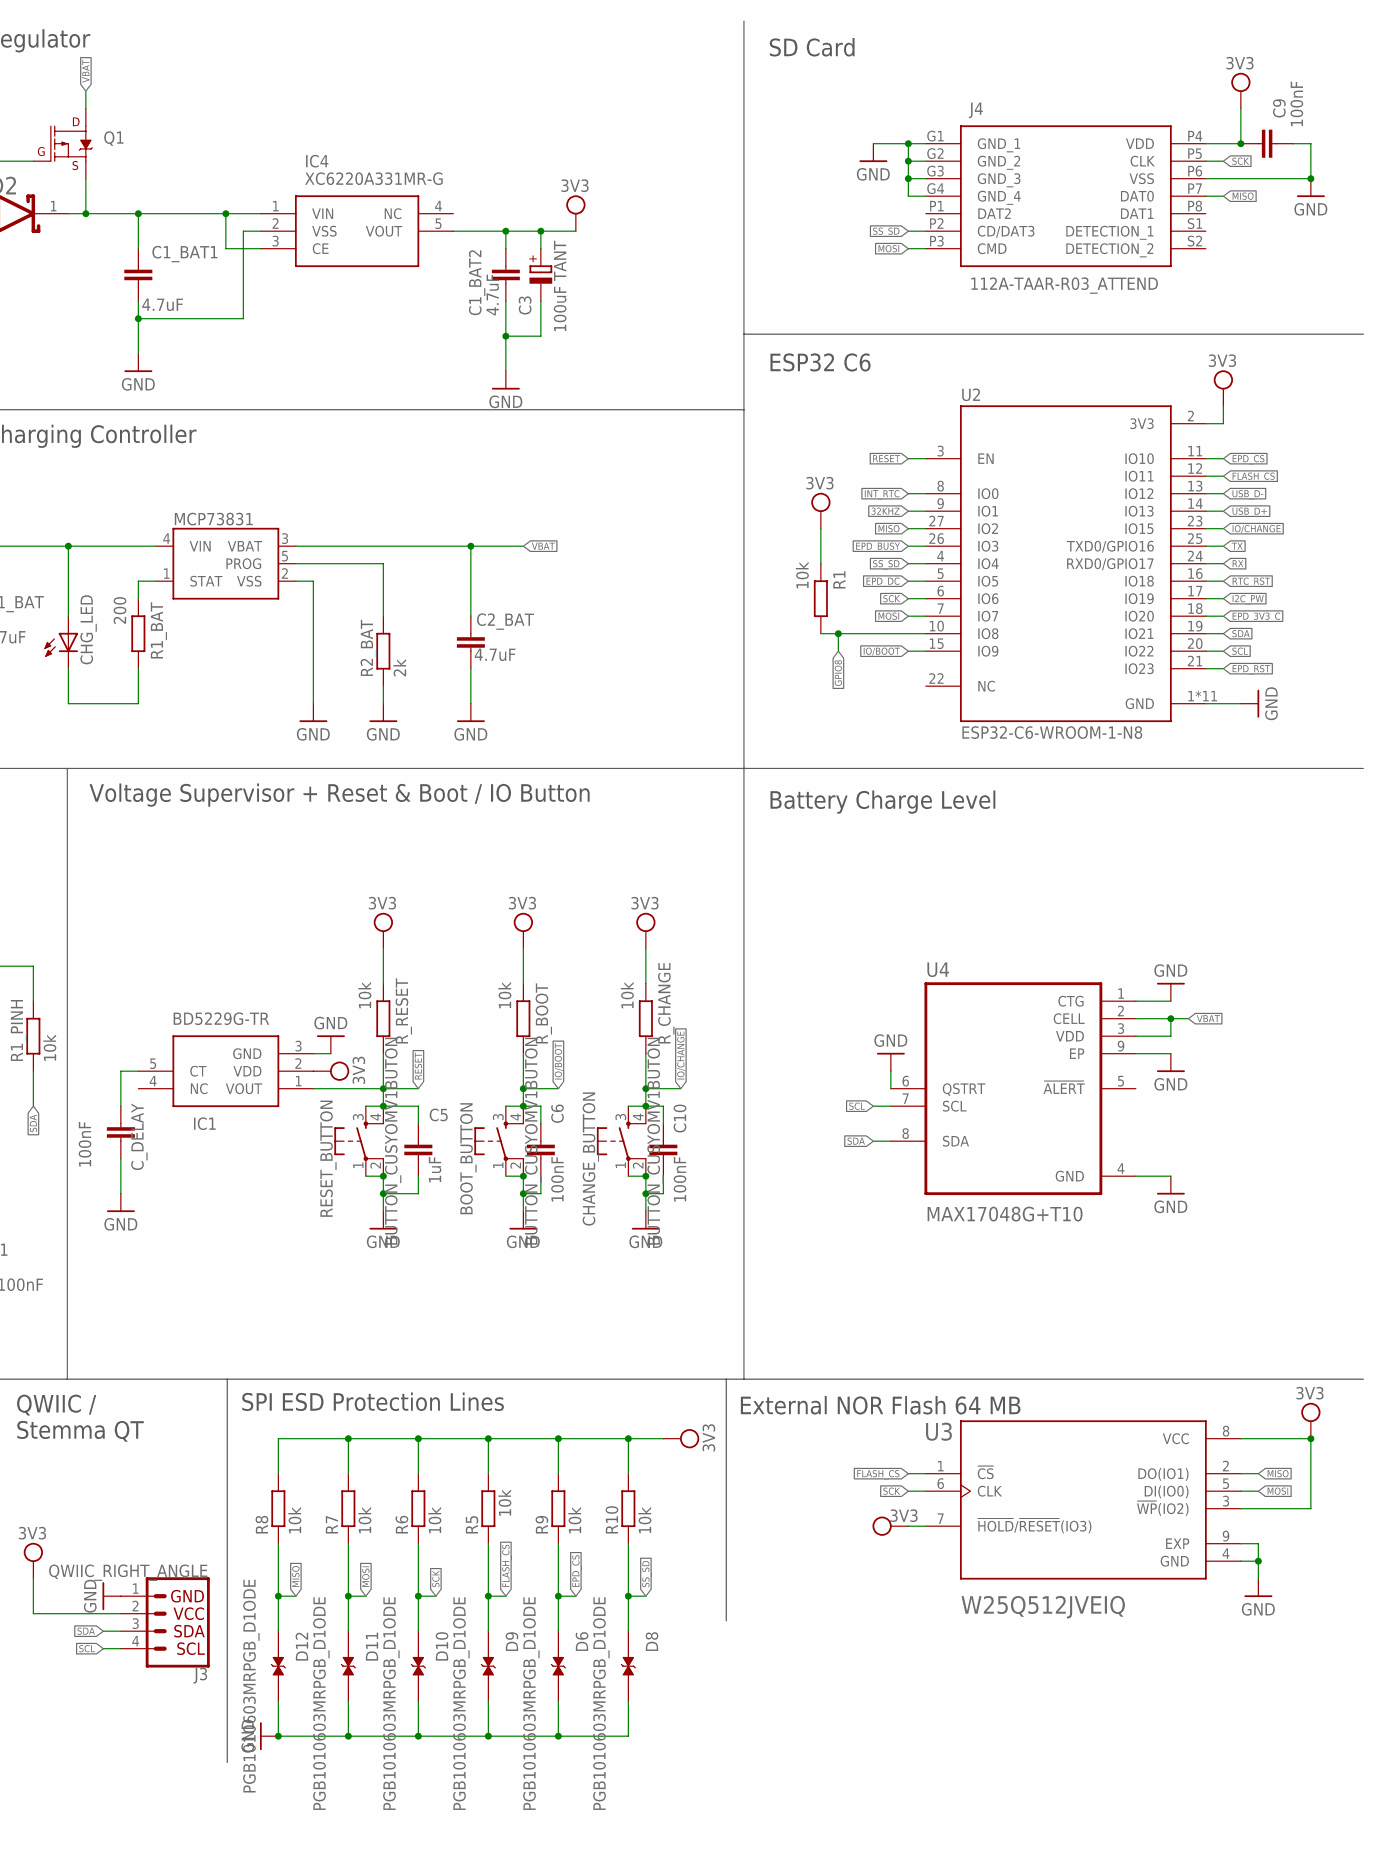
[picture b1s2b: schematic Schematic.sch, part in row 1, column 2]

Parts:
BOOT_BUTTON: BUTTON_CUSYOMV1BUTON; MYBUTTON
C1, C2, C4_USB, C6, C8, C9, C10: 100nF; ESP32_WROVER_EAGLE-LTSPICE_C0402
C1_BAT, C1_BAT1, C1_BAT2, C2_BAT, C5_USB: 4.7uF; ESP32_WROVER_EAGLE-LTSPICE_C0402
C3: 100uF TANT; RCL_CT3528
C4: 4.7uF/25V; ESP32_WROVER_EAGLE-LTSPICE_C0402
C5: 1uF; ESP32_WROVER_EAGLE-LTSPICE_C0402
C7: 10uF; ESP32_WROVER_EAGLE-LTSPICE_C0402
C10_SUPERCAP: CPH3225A; CAPCP3225X100N
CHANGE_BUTTON: BUTTON_CUSYOMV1BUTON; MYBUTTON
CHG_LED: ADAFRUIT_LEDCHIP-LED0603; ADAFRUIT_CHIP-LED0603
C_DELAY: 100nF; ESP32_WROVER_EAGLE-LTSPICE_C0402
D1: USBLC6-2SC6Y; SOT95P280X145-6N
D2, D7: ESP32_WROVER_AVX---SD0805S020S1R0_AVX_SD0805S020S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; ESP32_WROVER_AVX---SD0805S020S1R0_AVX_SD0805S020S1R0_0
D3, D4, D5: MBR0530MBR_SOD_DIODE; SOD3716X135N
D6, D8, D9, D10, D11, D12: PGB1010603MRPGB_D1ODE; DIOC1608X36N
EPD_C1, EPD_C2, EPD_C6, EPD_C7, EPD_C8, EPD_C9, EPD_C10, EPD_C11, EPD_C12: 1uF/50V; ESP32_WROVER_EAGLE-LTSPICE_C0402
EPD_C5: 0.1uF/50V; ESP32_WROVER_EAGLE-LTSPICE_C0402
IC1: BD5229G-TR; SOT95P280X125-5N
IC4: XC6220A331MR-G; SOT95P280X120-5N
J1: FH34SRJ-24S-0.5SH_99_; FH34SRJ24S05SH99
J2: SAMACSYS_PARTS_USB4110-GF-A; SAMACSYS_PARTS_USB4110GFA
J3: QWIIC_RIGHT_ANGLE; JST04_1MM_RA
J4: 112A-TAAR-R03_ATTEND; 112ATAARR03ATTEND
L1: 68uH; IND_4828-WE-TPC_WRE
MCP73831: ESP32_WROVER_SPARKFUN-IC-POWER_MCP73831; ESP32_WROVER_SPARKFUN-IC-POWER_SOT23-5
PFMF.050.1: ESP32C6_VARISTORPFMF_ESP32C6_VARISTORS; ESP32C6_VARISTOR_CT/CN1812
Q1, Q2: 20V/4.2A/52mΩ/1.4W; ESP32_WROVER_SPARKFUN-DISCRETESEMI_SOT23-3
Q3: SI1308EDL-T1-GE3; SOT65P210X110-3N
R1, R1_PINH, R1_PINH1, R2_PINH, R2_PINH1, R4, R5, R6, R7, R8, R9, R10: 10k; ESP32_WROVER_EAGLE-LTSPICE_R0402
R1_BAT: 200; ESP32_WROVER_EAGLE-LTSPICE_R0402
R1_PWRUSB: 100k; ESP32_WROVER_EAGLE-LTSPICE_R0402
R2: 2.2; ESP32_WROVER_EAGLE-LTSPICE_R0402
R2-USB, R2-USB1: 5k1; ESP32_WROVER_EAGLE-LTSPICE_R0402
R2_BAT: 2k; ESP32_WROVER_EAGLE-LTSPICE_R0402
R3: 0.47; ESP32_WROVER_EAGLE-LTSPICE_R0402
RESET_BUTTON: BUTTON_CUSYOMV1BUTON; MYBUTTON
R_BOOT: 10k; ESP32_WROVER_EAGLE-LTSPICE_R0402
R_CAPACITOR: 15; ESP32_WROVER_EAGLE-LTSPICE_R0402
R_CHANGE: 10k; ESP32_WROVER_EAGLE-LTSPICE_R0402
R_CL1: 10k; ESP32_WROVER_EAGLE-LTSPICE_R0402
R_RESET: 10k; ESP32_WROVER_EAGLE-LTSPICE_R0402
SENSOR2: BME688; ESP32_WROVER_BME680_PSON80P300X300X100-8N
SJ1: SJ
TP1, TP2, TP3, TP4, TP5, TP6, TP7, TP8, TP9, TP10, TP11, TP12, TP13, TP14, TP15, TP16, TP17: TPTP20R; TP20R
U1: DS3231SN#; SOIC127P1032X265-16N
U2: ESP32-C6-WROOM-1-N8; XCVR_ESP32-C6-WROOM-1-N8
U3: W25Q512JVEIQ; SON127P600X800X80-9N
U4: MAX17048G+T10; SON50P200X200X80-9N

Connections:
3V3: C1_BAT2.1, C3.+, C9.1, D7.2 (ANODE), IC1.2 (VDD), IC4.5 (VOUT), J3.2, J4.P4 (VDD), Q2.3 (D), R1.2, R1_PINH1.2, R2_PINH1.2, R5.2, R6.2, R7.2, R8.2, R9.2, R10.2, R_BOOT.2, R_CHANGE.2, R_CL1.2, R_RESET.2, TP16.TP, U1.2 (VCC), U2.2 (3V3), U3.3 (!WP!(IO2)), U3.7 (!HOLD!/!RESET!(IO3)), U3.8 (VCC)
32KHZ: R2_PINH1.1, U1.1 (32KHZ), U2.9 (IO1)
DN: D1.4 (I/O2_2), J2.A7, J2.B7
DP: D1.6 (I/O1_2), J2.A6, J2.B6
EPD_3V3: C7.2, EPD_C5.2, J1.15, J1.16, L1.2, Q2.2 (S), TP17.TP
EPD_3V3_C: Q2.1 (G), R_CL1.1, TP13.TP, U2.18 (IO20)
EPD_BUSY: J1.9, TP9.TP, U2.26 (IO3)
EPD_CS: D6.1, J1.12, R9.1, TP10.TP, U2.11 (IO10)
EPD_DC: J1.11, TP11.TP, U2.5 (IO5)
EPD_RST: J1.10, TP12.TP, U2.21 (IO23)
FLASH_CS: D9.1, R5.1, U2.12 (IO11), U3.1 (!CS)
GDR: J1.2, Q3.1 (G), R4.2
GND: BOOT_BUTTON.1, BOOT_BUTTON.2, C1.2, C1_BAT.2, C1_BAT1.2, C1_BAT2.2, C2.2, C2_BAT.2, C3.-, C4_USB.2, C5.2, C5_USB.2, C6.2, C7.1, C8.1, C9.2, C10.2, C10_SUPERCAP.1, CHANGE_BUTTON.1, CHANGE_BUTTON.2, C_DELAY.2, D1.2 (GND), D3.1 (K), D6.2, D8.2, D9.2, D10.2, D11.2, D12.2, EPD_C1.1, EPD_C2.1, EPD_C5.1, EPD_C6.1, EPD_C7.1, EPD_C8.1, EPD_C9.1, EPD_C10.1, EPD_C11.1, EPD_C12.1, IC1.3 (GND), IC4.2 (VSS), J1.8, J1.17, J1.MP1, J1.MP2, J2.A1, J2.A12, J2.B1, J2.B12, J2.MP1, J2.MP2, J2.MP3, J2.MP4, J3.1, J4.G1 (GND_1), J4.G2 (GND_2), J4.G3 (GND_3), J4.G4 (GND_4), J4.P6 (VSS), MCP73831.2 (VSS), R1_PWRUSB.1, R2.1, R2-USB.2, R2-USB1.1, R2_BAT.1, R4.1, RESET_BUTTON.1, RESET_BUTTON.2, SENSOR2.1 (GND), SENSOR2.5 (SDO), SENSOR2.7 (GND), SJ1.1, TP4.TP, TP5.TP, U1.13 (GND), U2.1 (GND), U2.28 (GND), U2.29_1 (GND), U2.29_2 (GND), U2.29_3 (GND)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
GPIO8: R1.1, U2.10 (IO8)
I2C_PW: C1.1, C2.1, R1_PINH.2, R2_PINH.2, SENSOR2.2 (CSB), SENSOR2.6 (VDDIO), SENSOR2.8 (VDD), U2.17 (IO19)
INT_RTC: R1_PINH1.1, TP15.TP, U1.3 (SQW/!INT), U2.8 (IO0)
IO/BOOT: BOOT_BUTTON.3, BOOT_BUTTON.4, C6.1, R_BOOT.1, U2.15 (IO9)
IO/CHANGE: C10.1, CHANGE_BUTTON.3, CHANGE_BUTTON.4, R_CHANGE.1, U2.23 (IO15)
MISO: D12.1, J4.P7 (DAT0), R8.1, TP6.TP, U2.27 (IO2), U3.2 (DO(IO1))
MOSI: D11.1, J1.14, J4.P3 (CMD), R7.1, TP7.TP, U2.7 (IO7), U3.5 (DI(IO0))
unnamed: J2.B5, R2-USB.1
unnamed: J2.A5, R2-USB1.2
unnamed: C1_BAT1.1, D2.1 (CATHODE), IC4.1 (VIN), IC4.3 (CE), Q1.2 (S)
unnamed: MCP73831.1 (STAT), R1_BAT.2
unnamed: MCP73831.5 (PROG), R2_BAT.2
unnamed: CHG_LED.C, R1_BAT.1
unnamed: C4.1, D3.2 (A), D4.1 (K)
unnamed: EPD_C6.2, J1.18
unnamed: EPD_C7.2, J1.19
unnamed: EPD_C8.2, J1.20
unnamed: C_DELAY.1, IC1.5 (CT)
unnamed: EPD_C10.2, J1.22
unnamed: D7.1 (CATHODE), R_CAPACITOR.2
unnamed: EPD_C12.2, J1.24
unnamed: EPD_C1.2, J1.4
unnamed: EPD_C2.2, J1.5
PREVGH: D5.1 (K), EPD_C9.2, J1.21
PREVGL: D4.2 (A), EPD_C11.2, J1.23
RESE: J1.3, Q3.2 (S), R3.2
RESE': R2.2, R3.1, SJ1.2
RESET: C5.1, IC1.1 (VOUT), RESET_BUTTON.3, RESET_BUTTON.4, R_RESET.1, U2.3 (EN)
RTC_RST: U1.4 (!RST), U2.16 (IO18)
RX: TP2.TP, U2.24 (RXD0/GPIO17)
SCK: D10.1, J1.13, J4.P5 (CLK), R6.1, TP8.TP, U2.6 (IO6), U3.6 (CLK)
SCL: J3.4, R2_PINH.1, SENSOR2.4 (SCK), U1.16 (SCL), U2.20 (IO22), U4.7 (SCL)
SDA: J3.3, R1_PINH.1, SENSOR2.3 (SDI), U1.15 (SDA), U2.19 (IO21), U4.8 (SDA)
SRC: C4.2, D5.2 (A), L1.1, Q3.3 (D)
SS_SD: D8.1, J4.P2 (CD/DAT3), R10.1, U2.4 (IO4)
TX: TP1.TP, U2.25 (TXD0/GPIO16)
USB_D+: D1.1 (I/O1_1), U2.14 (IO13)
USB_D-: D1.3 (I/O2_1), U2.13 (IO12)
VBAT: C2_BAT.1, MCP73831.3 (VBAT), Q1.3 (D), TP3.TP, U4.2 (CELL), U4.3 (VDD)
VBUS: C1_BAT.1, C4_USB.1, C5_USB.1, CHG_LED.A, D1.5 (VBUS), D2.2 (ANODE), MCP73831.4 (VIN), PFMF.050.1.2, Q1.1 (G), R1_PWRUSB.2, TP14.TP
VRTC: C8.2, C10_SUPERCAP.2, R_CAPACITOR.1, U1.14 (VBAT)
VUSB: J2.A4, J2.A9, J2.B4, J2.B9, PFMF.050.1.1

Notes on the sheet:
USB C connector & ESD protection
LDO Voltage Regulator
SD Card
ESP32 C6
Li-Po Battery Charging Controller
E-Paper Drive Circuit
Display Type Selector
E-Paper Display Header
EPD Power
Environmental Sensor BME688
Voltage Supervisor + Reset & Boot / IO Button
Battery Charge Level
RTC Module DS3231SN
Test Pads
QWIIC / Stemma QT
SPI ESD Protection Lines
External NOR Flash 64 MB

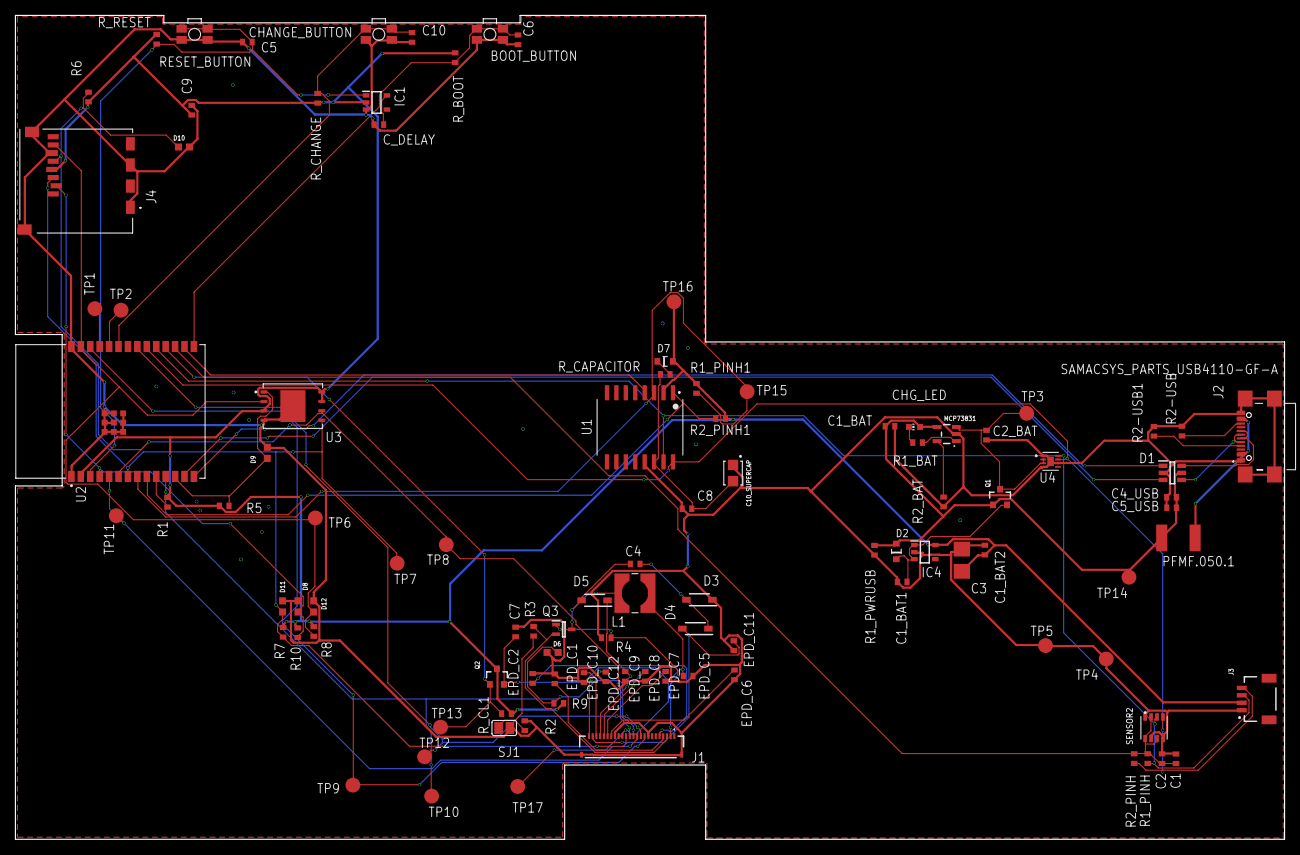
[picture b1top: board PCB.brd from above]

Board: 2 copper layers, 171.0 x 111.0 mm, 103 parts (0 on the bottom side), 55 nets.

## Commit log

2025-03-29 Schematic done; working on PCB board
2025-03-29 t3st
2025-04-06 Project finished
2025-04-10 README refactored
2025-04-10 README testing..
2025-04-15 Added 3D models to PCB layout
2025-04-16 Images added

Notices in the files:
parts and their libraries:
COPYRIGHT: Copyright (C) 2024 Ultra Librarian. All rights reserved.
